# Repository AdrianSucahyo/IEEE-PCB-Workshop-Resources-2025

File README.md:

# IEEE PCB Workshop Spring 2025

## Introduction
Welcome to the IEEE PCB Workshop Series for Spring 2025 at the University of Utah.

## General Information

We will be hosting these workshops over 9 weeks this semester, currently scheduled for Tuesdays at 5:15 PM to 6:15 PM beginning February 4th and ending April 15th. Sessions may go overtime to 6:45 PM depending on the topic covered. To help alleviate these longer sessions, food may be provided (tentatively planned). All planned dates are shown below.

The workshops will be held in WEB2230 unless otherwise specified.

There will be two main projects presented and all participants are invited to participate in designing, manufacturing, and assembling their own PCBs, which they will be able to keep at the end. The two projects to be presented are the following:
- Variable Switching Breadboard Power Supply
- ESP32 LED Matrix

__Workshop Goals__

- Introduction to PCB design
- Introduction to ECAD software (Altium | KiCAD)
    - Altium will be the ECAD software demonstrated during the session, however KiCAD planned to be supported (limited)
- Introduction to Schematic Layout
- Introduction to PCB Layout
- Basics of PCB Manufacturing
- Introduction to Soldering
    - We will offer different levels: Basic Through Hole, Intermediate Surface Mount, and Advanced Surface Mount
- Introduction to Verification and Debugging

## ECAD Software

### ALTIUM Designer (Highly Recommended)
Altium is the software that is going to be desmonstrated during the workshop and will be the easiest to follow along. All resources provided will be natively supported in Altium Designer.

If you plan to use Altium, please complete the instructions for registering and installing Altium on a personal machine. This allows us to immediately begin our workshop sessions without troubleshooting.

Altium License Instructions:
https://docs.google.com/document/d/1AU2HPewD7sdPoBuVvdMO27dwBopvW5h48ppQYsgPDJ0/edit?usp=sharing

### KiCAD

Please install KiCAD if you are not using Altium. While we do support this program, as KiCAD can import Altium files, we will be focusing on Altium Designer.

KiCAD Official Page:
https://www.kicad.org/

## Schedule

| DATE   | SESSION NAME | LINK |
|--------|--------------|------|
| Feb 4  | Introduction to Schematics (Power Supply) | [Week 01](https://github.com/AdrianSucahyo/IEEE-PCB-Workshop-Resources-2025/tree/main/Week01) |
| Feb 11 | Introduction to PCB Layout (Power Supply) | [Week 02](https://github.com/AdrianSucahyo/IEEE-PCB-Workshop-Resources-2025/tree/main/Week02) |
| Feb 18 | Intermediate Schematic Design (ESP32 LED Matrix) | [Week 03](https://github.com/AdrianSucahyo/IEEE-PCB-Workshop-Resources-2025/tree/main/Week03) |
| Feb 25 | Intermediate PCB Design (ESP32 LED Matrix) | [Week 04](https://github.com/AdrianSucahyo/IEEE-PCB-Workshop-Resources-2025/tree/main/Week04) |
| Mar 4  | Manufacturing and More | [Week 05](https://github.com/AdrianSucahyo/IEEE-PCB-Workshop-Resources-2025/tree/main/Week05) |
| Mar 18 | Introduction to Soldering (Power Supply - Surface Mount) | [Week 06](https://github.com/AdrianSucahyo/IEEE-PCB-Workshop-Resources-2025/tree/main/Week06) |
| Mar 25 | Introduction to Soldering (Power Supply - Through Hole) | [Week 07](https://github.com/AdrianSucahyo/IEEE-PCB-Workshop-Resources-2025/tree/main/Week07) |
| Apr 8  | Advanced Board Assembly (ESP32 Pick and Place) | [Week 08](https://github.com/AdrianSucahyo/IEEE-PCB-Workshop-Resources-2025/tree/main/Week08) |
| Apr 15 | Final Notes | [Week 09](https://github.com/AdrianSucahyo/IEEE-PCB-Workshop-Resources-2025/tree/main/Week09) |

While it is recommended to attend all sessions, we will provide the design and workshop files through a GitHub repository. To stay up to date, please be sure to follow along to not fall behind.

## Contact Info

- Questions may be routed to the IEEE email: ieee.studentbranch.uofu@gmail.com
- Updates are also posted on the IEEE / ECE discord: https://discord.gg/TMjhuDCCfy

## Sign-Up Flyer

Sign-Up Form:
https://forms.gle/mb3GaEBPHUk1RxPPA

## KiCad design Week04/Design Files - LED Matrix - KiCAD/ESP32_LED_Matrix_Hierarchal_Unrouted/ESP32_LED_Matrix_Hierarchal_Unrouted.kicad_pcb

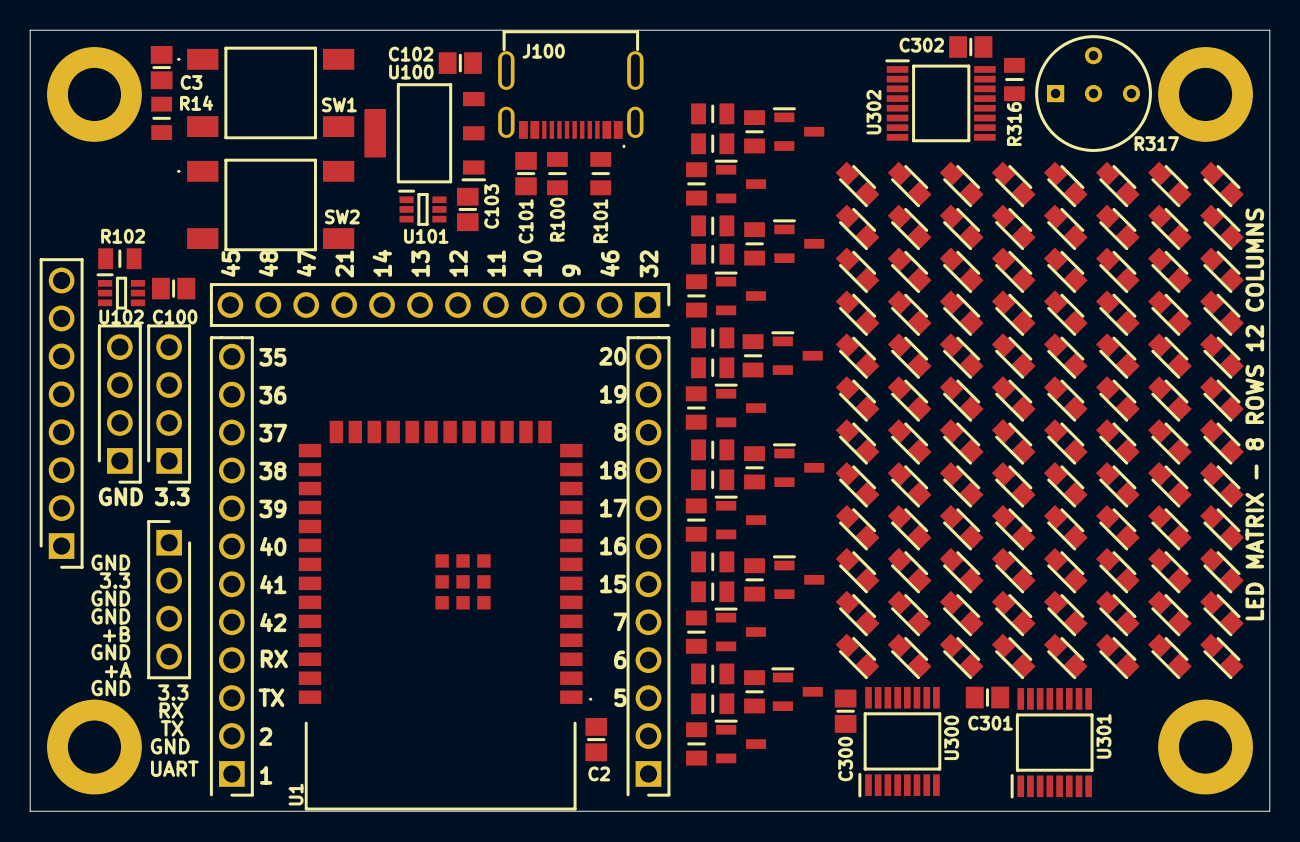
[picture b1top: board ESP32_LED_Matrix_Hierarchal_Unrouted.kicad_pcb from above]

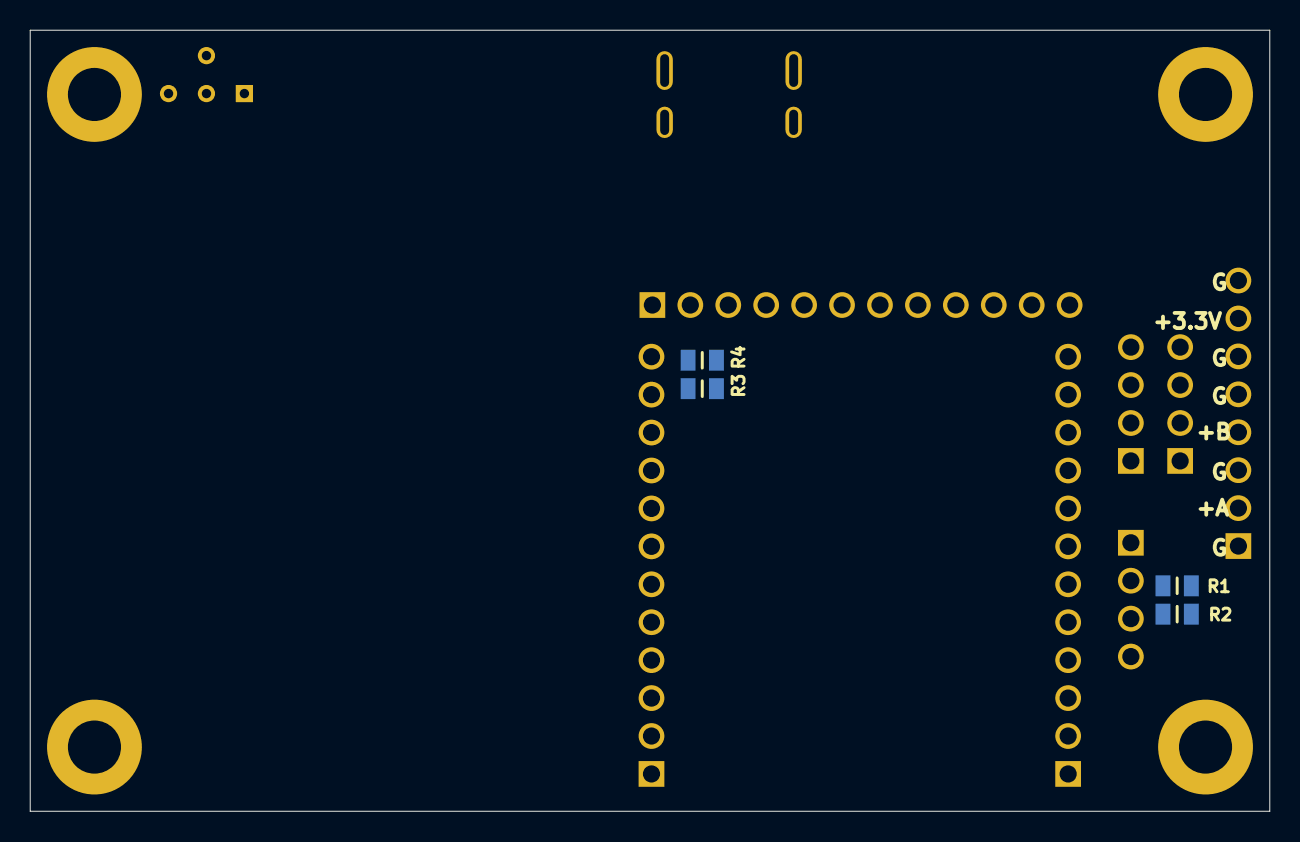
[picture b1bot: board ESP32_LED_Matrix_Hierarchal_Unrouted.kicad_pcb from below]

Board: 2 copper layers, 83.0 x 52.3 mm, 168 parts (4 on the bottom side), 97 nets, no tracks yet.

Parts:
C2, C100, C101, C102, C103, C300, C301, C302: 100n; CAP0805
C3: 1u; CAP0805
D200, D201, D202, D203, D204, D205, D206, D207, D208, D209, D210, D211, D212, D213, D214, D215, D216, D217, D218, D219, D220, D221, D222, D223, D224, D225, D226, D227, D228, D229, D230, D231, D232, D233, D234, D235, D236, D237, D238, D239, D240, D241, D242, D243, D244, D245, D246, D247, D248, D249, D250, D251, D252, D253, D254, D255, D256, D257, D258, D259, D260, D261, D262, D263, D264, D265, D266, D267, D268, D269, D270, D271, D272, D273, D274, D275, D276, D277, D278, D279, D280, D281, D282, D283, D284, D285, D286, D287, D288, D289, D290, D291, D292, D293, D294, D295: LED; LEDM2012X80N
H2, H3, H4: Header; Header_1X12
H5, H6, H7: 4-Pin Header; Header_1X4
H100: Header; Header_1X8
J100: USB C; USB TYPE C 12 PIN
Q300, Q301, Q302, Q303, Q304, Q305, Q306, Q307, Q308, Q309, Q310, Q311: SI2305; SOT23
R1, R2, R3, R4: 0; RESC0805
R14, R102, R304, R305, R306, R307, R312, R313, R314, R315, R322, R323, R324, R325: 10k; RESC0805
R100, R101: 5.11k; RESC0805
R300, R301, R302, R303, R308, R309, R310, R311, R318, R319, R320, R321: 100k; RESC0805
R316: 1k; RESC0805
R317: 50k; 3339P1103LF
SW1, SW2: TS04-66-73-BK-100-SMT; Tactile Button 6.0mm x 6.0mm
U1: ESP32-S3-WROOM-1-N8
U100: AZ1117CH2-3.3TRG1; SOT223
U101, U102: LM66100DCKR; SC70-6
U300, U301: 74HC595; TSSOP16
U302: STP08DP05TTR; TSSOP16

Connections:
+3.3: C2.1, C100.1, C103.1, C300.1, C301.1, C302.1, H2.1, H5.1, H6.1, H6.2, H6.3, H6.4, R14.1, U1.2, U101.6, U102.6, U300.10, U300.16, U301.10, U301.16, U302.16
COL0: D200.2, D212.2, D224.2, D236.2, D248.2, D260.2, D272.2, D284.2, Q300.3
COL1: D201.2, D213.2, D225.2, D237.2, D249.2, D261.2, D273.2, D285.2, Q304.3
COL2: D202.2, D214.2, D226.2, D238.2, D250.2, D262.2, D274.2, D286.2, Q308.3
COL3: D203.2, D215.2, D227.2, D239.2, D251.2, D263.2, D275.2, D287.2, Q301.3
COL4: D204.2, D216.2, D228.2, D240.2, D252.2, D264.2, D276.2, D288.2, Q305.3
COL5: D205.2, D217.2, D229.2, D241.2, D253.2, D265.2, D277.2, D289.2, Q309.3
COL6: D206.2, D218.2, D230.2, D242.2, D254.2, D266.2, D278.2, D290.2, Q302.3
COL7: D207.2, D219.2, D231.2, D243.2, D255.2, D267.2, D279.2, D291.2, Q306.3
COL8: D208.2, D220.2, D232.2, D244.2, D256.2, D268.2, D280.2, D292.2, Q310.3
COL9: D209.2, D221.2, D233.2, D245.2, D257.2, D269.2, D281.2, D293.2, Q303.3
COL10: D210.2, D222.2, D234.2, D246.2, D258.2, D270.2, D282.2, D294.2, Q307.3
COL11: D211.2, D223.2, D235.2, D247.2, D259.2, D271.2, D283.2, D295.2, Q311.3
COL_DS: H2.5, U1.7, U300.14
COL_OE: H2.4, U1.6, U300.13, U301.13
COL_SH_CP: H2.2, U1.4, U300.11, U301.11
COL_SIG0: R304.1, U300.1
COL_SIG1: R312.1, U300.2
COL_SIG2: R322.1, U300.3
COL_SIG3: R305.1, U300.4
COL_SIG4: R313.1, U300.5
COL_SIG5: R323.1, U300.6
COL_SIG6: R306.1, U300.7
COL_SIG7: R314.1, U301.1
COL_SIG8: R324.1, U301.2
COL_SIG9: R307.1, U301.3
COL_SIG10: R315.1, U301.4
COL_SIG11: R325.1, U301.5
COL_ST_CP: H2.3, U1.5, U300.12, U301.12
EXT_SUPP_EN: R102.1, U101.3, U102.5
GND: C2.2, C3.2, C100.2, C101.2, C102.2, C103.2, C300.2, C301.2, C302.2, H5.4, H7.1, H7.2, H7.3, H7.4, H100.1, H100.3, H100.5, H100.6, H100.8, J100.1, J100.2, J100.3, J100.14, J100.15, J100.16, R100.1, R101.1, R317.3, SW1.1, SW1.2, SW2.1, SW2.2, U1.1, U1.40, U1.41, U1.42, U1.43, U1.44, U1.45, U1.46, U1.47, U1.48, U1.49, U100.2, U100.4, U101.2, U101.5, U102.2, U300.8, U301.8, U302.1
GPIO1: H3.1, U1.39
GPIO2: H3.2, U1.38
GPIO3: H4.1, U1.15
GPIO8: H2.10, U1.12
GPIO9: H4.3, U1.17
GPIO10: H4.4, U1.18
GPIO11: H4.5, U1.19
GPIO12: H4.6, U1.20
GPIO13: H4.7, U1.21
GPIO14: H4.8, U1.22
GPIO15: H2.6, U1.8, U302.3
GPIO16: H2.7, U1.9, U302.4
GPIO17: H2.8, U1.10, U302.13
GPIO18: H2.9, U1.11, U302.2
GPIO19: H2.11, R3.1
GPIO20: H2.12, R4.1
GPIO21: H4.9, U1.23
GPIO35: H3.12, U1.28
GPIO36: H3.11, U1.29
GPIO37: H3.10, U1.30
GPIO38: H3.9, U1.31
GPIO39: H3.8, U1.32
GPIO40: H3.7, U1.33
GPIO41: H3.6, U1.34
GPIO42: H3.5, U1.35
GPIO45: H4.12, U1.26
GPIO46: H4.2, U1.16
GPIO47: H4.10, U1.24
GPIO48: H4.11, U1.25
MCU_BOOT: SW2.3, SW2.4, U1.27
MCU_EN: C3.1, R14.2, SW1.3, SW1.4, U1.3
NetC101_1: C101.1, J100.4, J100.13, U100.1
NetH5_2: H5.2, R1.2
NetH5_3: H5.3, R2.2
NetJ100_5: J100.5, R100.2
NetJ100_11: J100.11, R101.2
NetQ300_1: Q300.1, R300.2, R304.2
NetQ301_1: Q301.1, R301.2, R305.2
NetQ302_1: Q302.1, R302.2, R306.2
NetQ303_1: Q303.1, R303.2, R307.2
NetQ304_1: Q304.1, R308.2, R312.2
NetQ305_1: Q305.1, R309.2, R313.2
NetQ306_1: Q306.1, R310.2, R314.2
NetQ307_1: Q307.1, R311.2, R315.2
NetQ308_1: Q308.1, R318.2, R322.2
NetQ309_1: Q309.1, R319.2, R323.2
NetQ310_1: Q310.1, R320.2, R324.2
NetQ311_1: Q311.1, R321.2, R325.2
NetR316_1: R316.1, U302.15
NetR316_2: R316.2, R317.1, R317.2
NetU300_9: U300.9, U301.14
ROW0: D200.1, D201.1, D202.1, D203.1, D204.1, D205.1, D206.1, D207.1, D208.1, D209.1, D210.1, D211.1, U302.5
ROW1: D212.1, D213.1, D214.1, D215.1, D216.1, D217.1, D218.1, D219.1, D220.1, D221.1, D222.1, D223.1, U302.6
ROW2: D224.1, D225.1, D226.1, D227.1, D228.1, D229.1, D230.1, D231.1, D232.1, D233.1, D234.1, D235.1, U302.7
ROW3: D236.1, D237.1, D238.1, D239.1, D240.1, D241.1, D242.1, D243.1, D244.1, D245.1, D246.1, D247.1, U302.8
ROW4: D248.1, D249.1, D250.1, D251.1, D252.1, D253.1, D254.1, D255.1, D256.1, D257.1, D258.1, D259.1, U302.9
ROW5: D260.1, D261.1, D262.1, D263.1, D264.1, D265.1, D266.1, D267.1, D268.1, D269.1, D270.1, D271.1, U302.10
ROW6: D272.1, D273.1, D274.1, D275.1, D276.1, D277.1, D278.1, D279.1, D280.1, D281.1, D282.1, D283.1, U302.11
ROW7: D284.1, D285.1, D286.1, D287.1, D288.1, D289.1, D290.1, D291.1, D292.1, D293.1, D294.1, D295.1, U302.12
UPDI_RX: H3.4, R1.1, U1.36
UPDI_TX: H3.3, R2.1, U1.37
USB_D_N: J100.8, J100.10, R3.2, U1.13
USB_D_P: J100.7, J100.9, R4.2, U1.14
USB_SUPP_EN: C102.1, U100.3, U101.1, U102.3
VCC_1: H100.2, Q300.2, Q301.2, Q302.2, Q303.2, Q304.2, Q305.2, Q306.2, Q307.2, Q308.2, Q309.2, Q310.2, Q311.2, R300.1, R301.1, R302.1, R303.1, R308.1, R309.1, R310.1, R311.1, R318.1, R319.1, R320.1, R321.1
V_MCU: H100.7, R102.2, U102.1

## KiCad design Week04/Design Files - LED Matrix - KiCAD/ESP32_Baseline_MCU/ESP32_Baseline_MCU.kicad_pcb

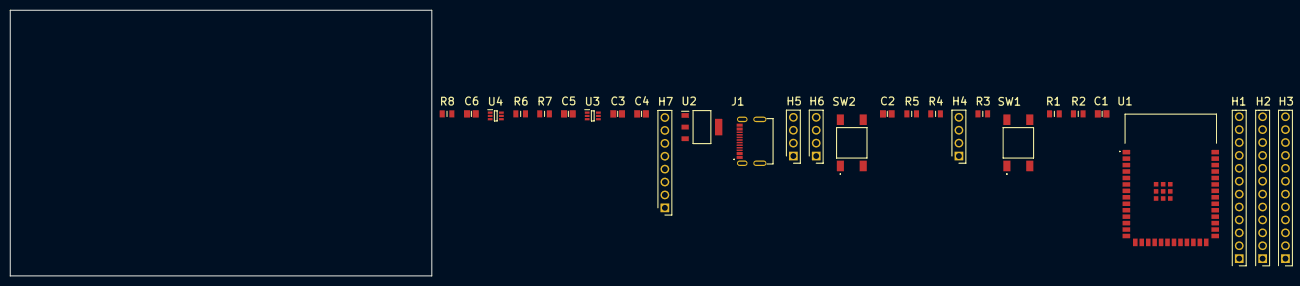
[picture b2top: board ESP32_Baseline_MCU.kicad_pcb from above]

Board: 2 copper layers, 83.0 x 52.3 mm, 28 parts (0 on the bottom side), 49 nets, no tracks yet.

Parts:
C1, C3, C4, C5, C6: 100n; CAP0805
C2: 1u; CAP0805
H1, H2, H3: Header; Header_1X12
H4, H5, H6: 4-Pin Header; Header_1X4
H7: Header; Header_1X8
J1: USB C; USB TYPE C 12 PIN
R1, R2, R4, R5: 0; RESC0805
R3, R8: 10k; RESC0805
R6, R7: 5.11k; RESC0805
SW1, SW2: TS04-66-73-BK-100-SMT; Tactile Button 6.0mm x 6.0mm
U1: ESP32-S3-WROOM-1-N8
U2: AZ1117CH2-3.3TRG1; SOT223
U3, U4: LM66100DCKR; SC70-6

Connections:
+3.3: C1.1, C5.1, C6.1, H1.1, H4.1, H5.1, H5.2, H5.3, H5.4, R3.1, U1.2, U3.6, U4.6
EXT_SUPP_EN: R8.1, U3.5, U4.3
GND: C1.2, C2.2, C3.2, C4.2, C5.2, C6.2, H4.4, H6.1, H6.2, H6.3, H6.4, H7.1, H7.3, H7.5, H7.6, H7.8, J1.1, J1.2, J1.3, J1.14, J1.15, J1.16, R6.1, R7.1, SW1.1, SW1.2, SW2.1, SW2.2, U1.1, U1.40, U1.41, U1.42, U1.43, U1.44, U1.45, U1.46, U1.47, U1.48, U1.49, U2.2, U2.4, U3.2, U4.2, U4.5
GPIO1: H2.1, U1.39
GPIO2: H2.2, U1.38
GPIO3: H3.1, U1.15
GPIO4: H1.2, U1.4
GPIO5: H1.3, U1.5
GPIO6: H1.4, U1.6
GPIO7: H1.5, U1.7
GPIO8: H1.10, U1.12
GPIO9: H3.3, U1.17
GPIO10: H3.4, U1.18
GPIO11: H3.5, U1.19
GPIO12: H3.6, U1.20
GPIO13: H3.7, U1.21
GPIO14: H3.8, U1.22
GPIO15: H1.6, U1.8
GPIO16: H1.7, U1.9
GPIO17: H1.8, U1.10
GPIO18: H1.9, U1.11
GPIO19: H1.11, R1.1
GPIO20: H1.12, R2.1
GPIO21: H3.9, U1.23
GPIO35: H2.12, U1.28
GPIO36: H2.11, U1.29
GPIO37: H2.10, U1.30
GPIO38: H2.9, U1.31
GPIO39: H2.8, U1.32
GPIO40: H2.7, U1.33
GPIO41: H2.6, U1.34
GPIO42: H2.5, U1.35
GPIO45: H3.12, U1.26
GPIO46: H3.2, U1.16
GPIO47: H3.10, U1.24
GPIO48: H3.11, U1.25
MCU_BOOT: SW2.3, SW2.4, U1.27
MCU_EN: C2.1, R3.2, SW1.3, SW1.4, U1.3
NetC3_1: C3.1, J1.4, J1.13, U2.1
NetH4_2: H4.2, R4.2
NetH4_3: H4.3, R5.2
NetJ1_5: J1.5, R6.2
NetJ1_11: J1.11, R7.2
UPDI_RX: H2.4, R4.1, U1.36
UPDI_TX: H2.3, R5.1, U1.37
USB_D_N: J1.8, J1.10, R1.2, U1.13
USB_D_P: J1.7, J1.9, R2.2, U1.14
USB_SUPP_EN: C4.1, U2.3, U3.3, U4.1
V_MCU: H7.7, R8.2, U3.1

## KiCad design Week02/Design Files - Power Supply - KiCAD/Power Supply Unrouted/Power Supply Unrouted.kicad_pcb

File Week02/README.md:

# WEEK 02 RESOURCES
## Overview

Feb 11th, 2025

- Covered the included slides content
- Introduced the basic functionality of Altium with regards to PCB layout
- Demonstrated the steps and basic guidelines for layout

Next Steps
- If you'd like to have your own design of the power supply manufactured, be sure to complete the layout by around March 1st.
- We will be holding a final workshop session March 4th to do final design reviews and getting everything ready for manufacturing.

## Files
### Week02-Files.zip
Altium Files and Library for the Week02 Workshop. Includes all necessary files to follow along in the session.
The files include a partially complete PCB layout (unrouted - parts placed for routing) and a completed design for reference.

### Altium Workshop Week 2_ PCB.pdf
Workshop introduction presentation. Used to cover a couple missed topics from Week01, and introduce PCB layout. Note that only the intro is covered, additional content was covered in real time.

### Week02-Files-KiCAD.zip
KiCAD Files and Library for the Week02 Workshop. Essentially a mirror of the Altium files but in KiCAD

NOTE: 3D Models for the KiCAD are not loading properly, the source of the issue is currently unknown on our end (likely due to importing an Altium component library). Footprints are correct however and should be good to use.

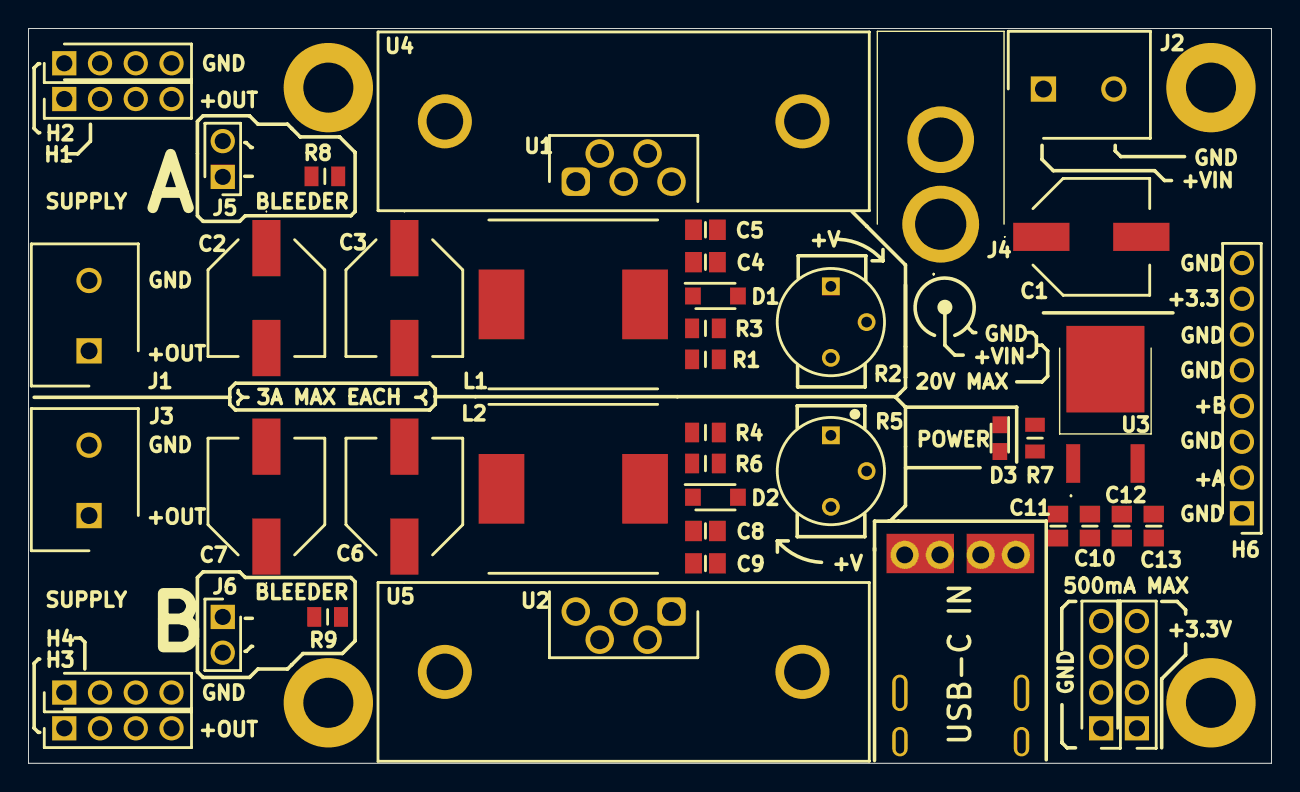
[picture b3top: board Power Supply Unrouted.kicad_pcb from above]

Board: 2 copper layers, 88.3 x 52.2 mm, 46 parts (0 on the bottom side), 14 nets, no tracks yet.

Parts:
C1, C2, C3, C6, C7: EEE-FN1V271UP; EEHZT1E331UP
C4, C8, C10, C13: 1u; CAP0805
C5, C9, C11, C12: 100n; CAP0805
D1, D2: V3FM10-M3_H; DO-219AB
D3: LED; LEDM2012X80N
H1, H2, H3, H4, H5, H7: Header; Header_1X4
H6: Header; Header_1X8
J1, J2, J3: 691137710002; SHDR2W70P0X500_1X2_1000X750X1160P
J4: PJ-037AH; PJ037AH
J5, J6: 90120-0762; HDRV2W35P0X254_1X2_508X249X560P
L1, L2: SRR1210-151M; INDPM120120X1000N-D
R1, R4, R7: 750; RESC0805
R2, R5: 50k; 3339P1103LF
R3, R6, R8, R9: 3.3k; RESC0805
U1, U2: LM2576WT; TO-220-5
U3: UA78M33CKVURG3; TO-252-3
U4, U5: 637-10ABPE; 63710ABPE
USB-C IN: USB-PD; USB_C-PD

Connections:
+3.3: C12.1, C13.1, H5.1, H5.2, H5.3, H5.4, H6.7, R7.1, U3.3
GND: C1.2, C2.2, C3.2, C4.2, C5.2, C6.2, C7.2, C8.2, C9.2, C10.2, C11.2, C12.2, C13.2, D1.2, D2.2, D3.1, H2.1, H2.2, H2.3, H2.4, H4.1, H4.2, H4.3, H4.4, H6.1, H6.3, H6.5, H6.6, H6.8, H7.1, H7.2, H7.3, H7.4, J1.2, J2.2, J3.2, J4.2, R3.2, R6.2, R8.2, R9.2, U1.3, U1.5, U2.3, U2.5, U3.2, U4.1, U4.2, U5.1, U5.2, USB-C IN.2
NetD1_1: D1.1, L1.1, U1.2
NetD2_1: D2.1, L2.1, U2.2
NetD3_2: D3.2, R7.2
NetJ5_2: J5.2, R8.1
NetJ6_2: J6.2, R9.1
NetR1_2: R1.2, R2.1
NetR2_2: R2.2, R2.3, R3.1, U1.4
NetR4_2: R4.2, R5.1
NetR5_2: R5.2, R5.3, R6.1, U2.4
VCC_1: C2.1, C3.1, H1.1, H1.2, H1.3, H1.4, H6.2, J1.1, J5.1, L1.2, R1.1
VCC_2: C6.1, C7.1, H3.1, H3.2, H3.3, H3.4, H6.4, J3.1, J6.1, L2.2, R4.1
V_IN: C1.1, C4.1, C5.1, C8.1, C9.1, C10.1, C11.1, J2.1, J4.1, U1.1, U2.1, U3.1, USB-C IN.1

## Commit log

2025-01-30 Initial Setup of Repository
2025-01-30 Commit Main Readme Changes
2025-01-31 Added Preliminary Library Files
2025-02-04 Added Week 1 Altium Files
2025-02-04 Updated Schematic Libraries and Footprints
2025-02-04 Zipped up WK01 Design Files
2025-02-04 Added week 1 slides
2025-02-04 Updated Zip Files
2025-02-04 Added LM2576 Datasheet
2025-02-05 Updated Week01 Notes and KiCAD
2025-02-05 Update README.md Links
2025-02-11 Added Project files and Powerpoint presentation
2025-02-11 Delete Week02/Altium Workshop Week 2_ PCB.pptx
    I'll upload .pdf instead
2025-02-11 Added presentation as PDF
2025-02-11 Added ISO 7010 signs and TI papers
2025-02-11 Updated Week02 Materials
2025-02-13 Update README.md for Week02
2025-02-18 Updated Week03 Resources
2025-02-23 Updated Week03 README
2025-02-25 Updated Week04 Altium Files
2025-02-25 Updated Week04 Resources
2025-03-09 Generated Gerber Files
2025-04-01 Updated Week06 Resources
2025-04-15 Added test firmware to Week07
